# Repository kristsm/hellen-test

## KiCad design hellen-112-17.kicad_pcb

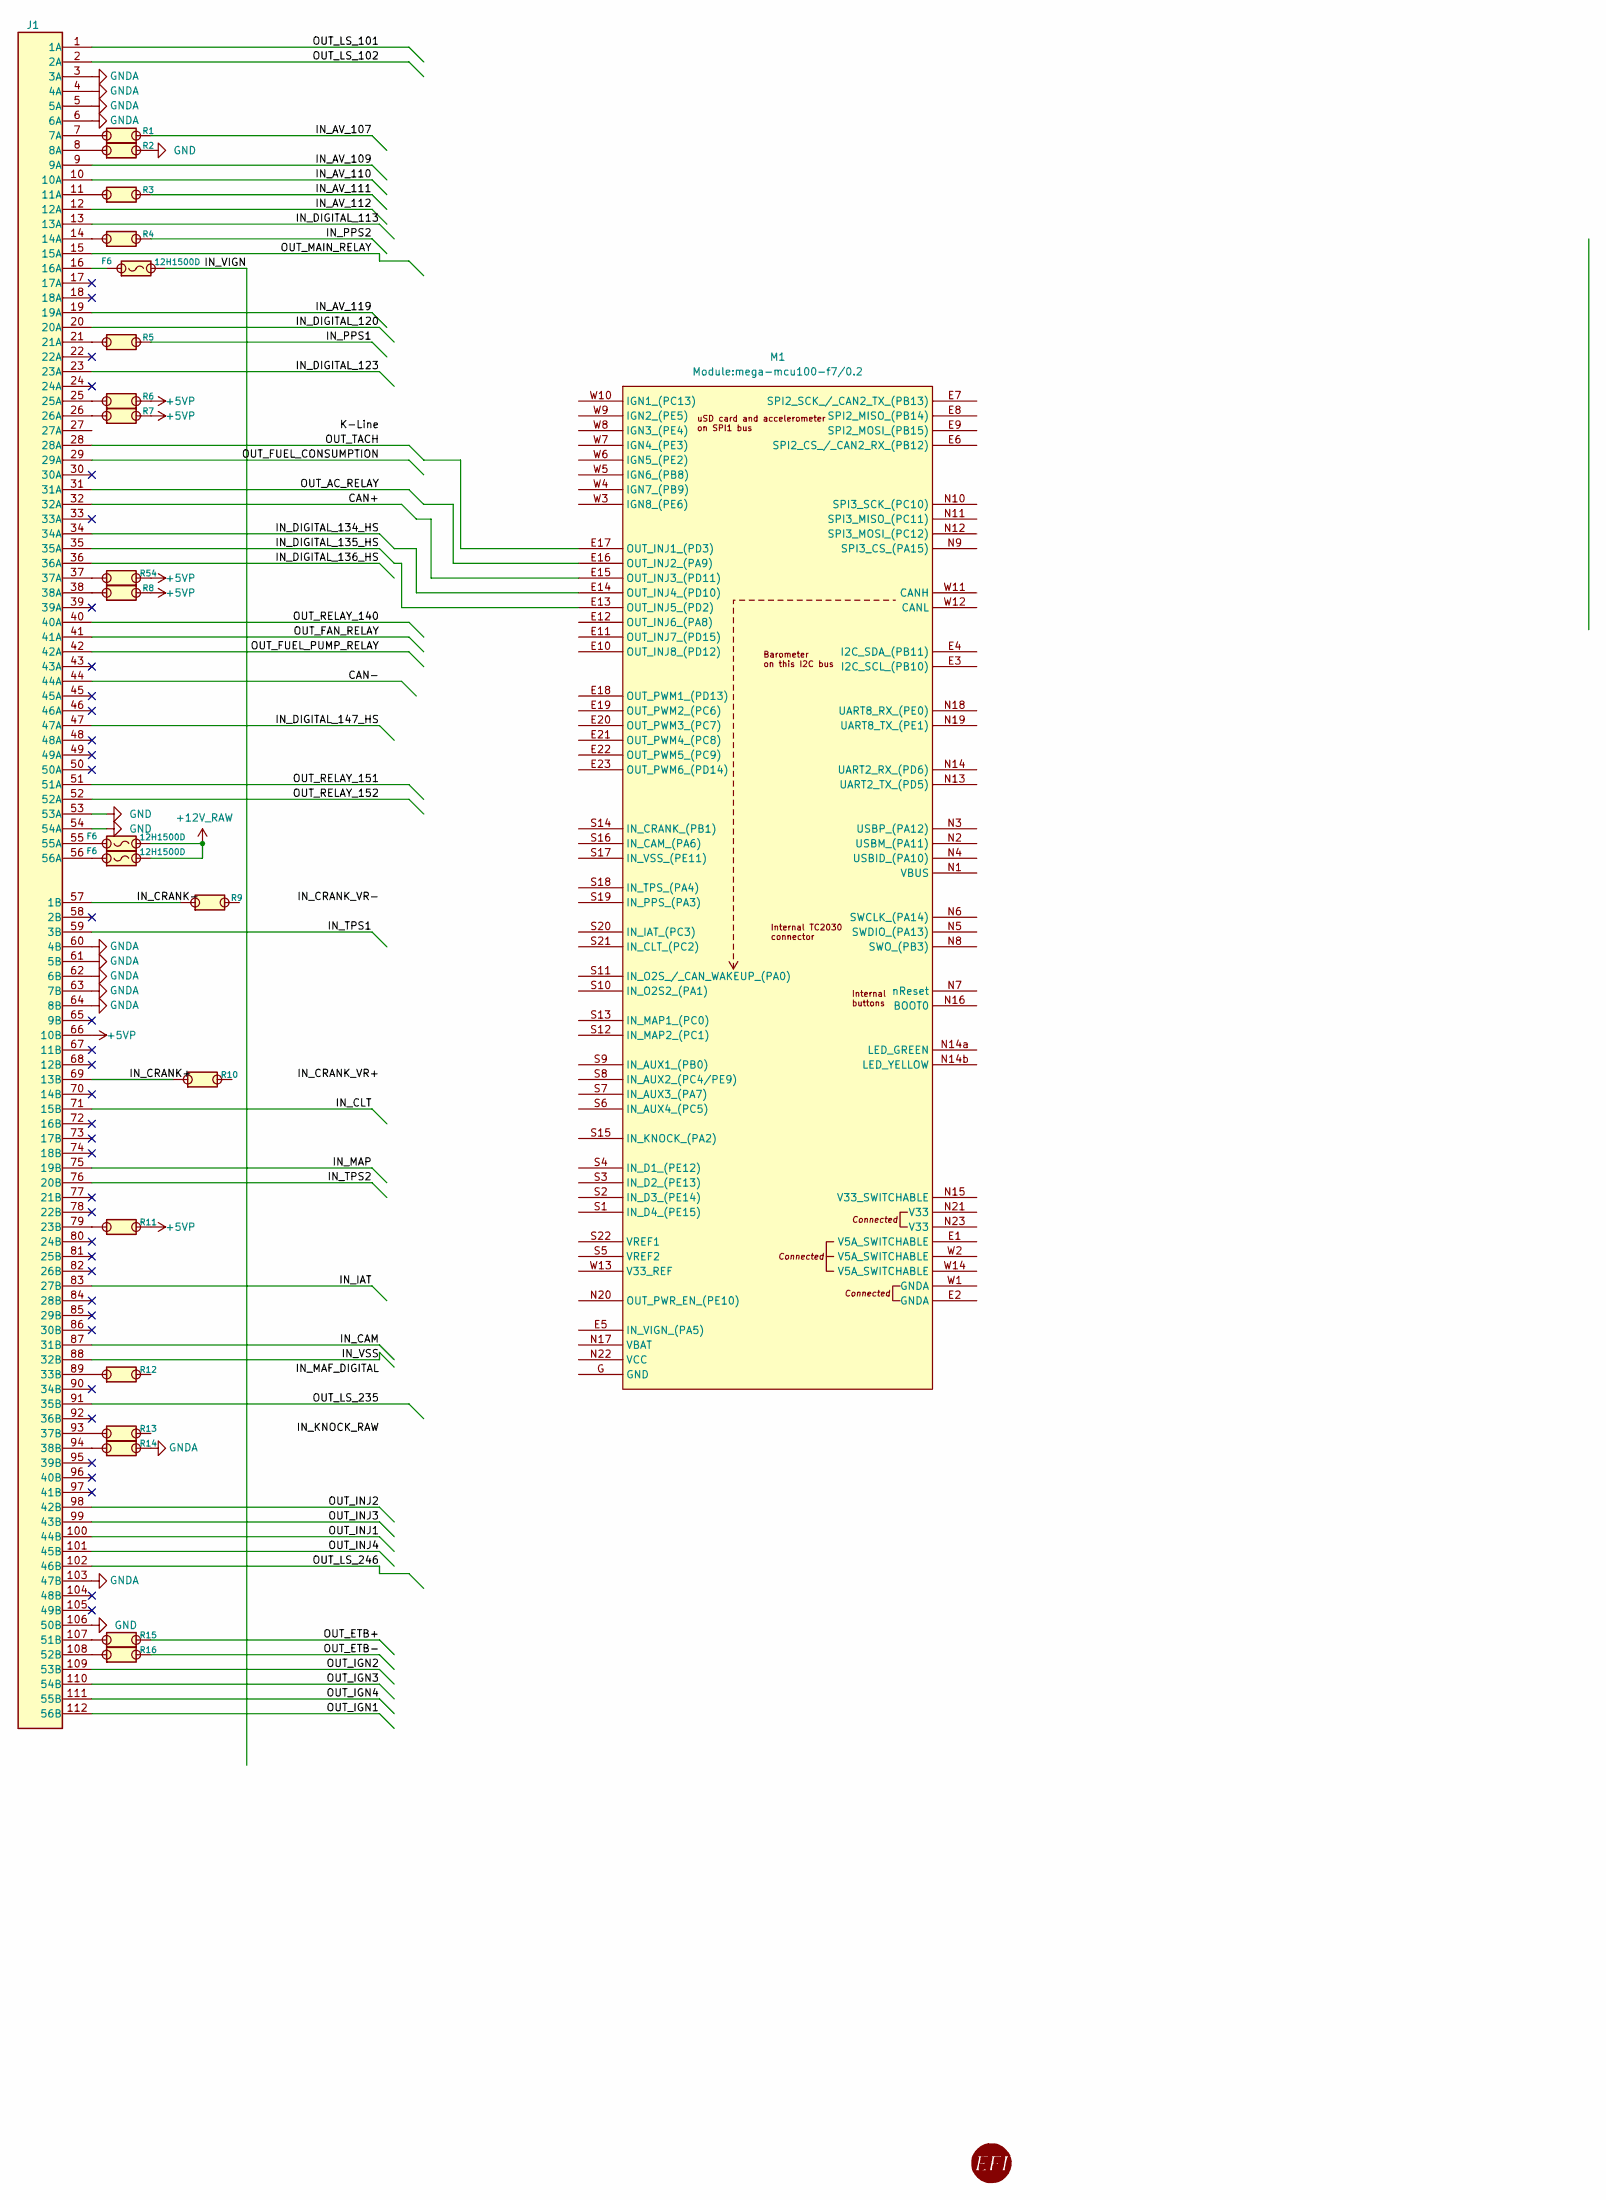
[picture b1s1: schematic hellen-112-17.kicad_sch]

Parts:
F6: 12H1500D; PAD-1206-PAD; LCSC C182446
G4: RUSEFI_LOGO; rusefi_logo
J1: rusefi_2x56_pin_conn; rusefi_2x56_pin_connector
M1: Module:mega-mcu100-f7/0.2; mega-mcu100-f7
R1, R2, R3, R4, R5, R6, R7, R8, R9, R10, R11, R12, R13, R14, R15, R16, R54: Jumper-Pad-Pad; PAD-0805-PAD; LCSC C17477

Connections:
+5VP: J1.66 (10B), R6.2, R7.2, R8.2, R11.2, R54.2
/CAN+: J1.32 (32A), M1.E15 (OUT_INJ3_(PD11))
/CAN-: J1.44 (44A)
/IN_AV_107: R1.2
/IN_AV_109: J1.9 (9A)
/IN_AV_110: J1.10 (10A)
/IN_AV_111: R3.2
/IN_AV_112: J1.12 (12A)
/IN_AV_119: J1.19 (19A)
/IN_CAM: J1.87 (31B)
/IN_CLT: J1.71 (15B)
/IN_CRANK+: J1.69 (13B), R10.1
/IN_CRANK-: J1.57 (1B), R9.1
/IN_DIGITAL_113: J1.13 (13A)
/IN_DIGITAL_120: J1.20 (20A)
/IN_DIGITAL_123: J1.23 (23A)
/IN_DIGITAL_134_HS: J1.34 (34A), M1.E14 (OUT_INJ4_(PD10))
/IN_DIGITAL_135_HS: J1.35 (35A), M1.E13 (OUT_INJ5_(PD2))
/IN_DIGITAL_136_HS: J1.36 (36A)
/IN_DIGITAL_147_HS: J1.47 (47A)
/IN_IAT: J1.83 (27B)
/IN_MAP: J1.75 (19B)
/IN_PPS1: R5.2
/IN_PPS2: R4.2
/IN_TPS1: J1.59 (3B)
/IN_TPS2: J1.76 (20B)
/IN_VSS: J1.88 (32B)
/OUT_AC_RELAY: J1.31 (31A), M1.E16 (OUT_INJ2_(PA9))
/OUT_ETB+: R15.2
/OUT_ETB-: R16.2
/OUT_FAN_RELAY: J1.41 (41A)
/OUT_FUEL_CONSUMPTION: J1.29 (29A)
/OUT_FUEL_PUMP_RELAY: J1.42 (42A)
/OUT_IGN1: J1.112 (56B)
/OUT_IGN2: J1.109 (53B)
/OUT_IGN3: J1.110 (54B)
/OUT_IGN4: J1.111 (55B)
/OUT_INJ1: J1.100 (44B)
/OUT_INJ2: J1.98 (42B)
/OUT_INJ3: J1.99 (43B)
/OUT_INJ4: J1.101 (45B)
/OUT_LS_101: J1.1 (1A)
/OUT_LS_102: J1.2 (2A)
/OUT_LS_235: J1.91 (35B)
/OUT_LS_246: J1.102 (46B)
/OUT_MAIN_RELAY: J1.15 (15A)
/OUT_RELAY_140: J1.40 (40A)
/OUT_RELAY_151: J1.51 (51A)
/OUT_RELAY_152: J1.52 (52A)
/OUT_TACH: J1.28 (28A), M1.E17 (OUT_INJ1_(PD3))
GND: J1.53 (53A), J1.54 (54A), J1.106 (50B), R2.2
GNDA: J1.3 (3A), J1.4 (4A), J1.5 (5A), J1.6 (6A), J1.60 (4B), J1.61 (5B), J1.62 (6B), J1.63 (7B), J1.64 (8B), J1.103 (47B), R14.2
unnamed: J1.7 (7A), R1.1
unnamed: J1.8 (8A), R2.1
unnamed: J1.11 (11A), R3.1
unnamed: J1.14 (14A), R4.1
unnamed 58: J1.16 (16A); also elsewhere on the board
unnamed: J1.21 (21A), R5.1
unnamed: J1.79 (23B), R11.1
unnamed: J1.25 (25A), R6.1
unnamed: J1.26 (26A), R7.1
unnamed: J1.89 (33B), R12.1
unnamed: J1.37 (37A), R54.1
unnamed: J1.93 (37B), R13.1
unnamed: J1.38 (38A), R8.1
unnamed: J1.94 (38B), R14.1
unnamed: J1.107 (51B), R15.1
unnamed: J1.108 (52B), R16.1
unnamed 70: J1.55 (55A); also elsewhere on the board
unnamed 71: J1.56 (56A); also elsewhere on the board

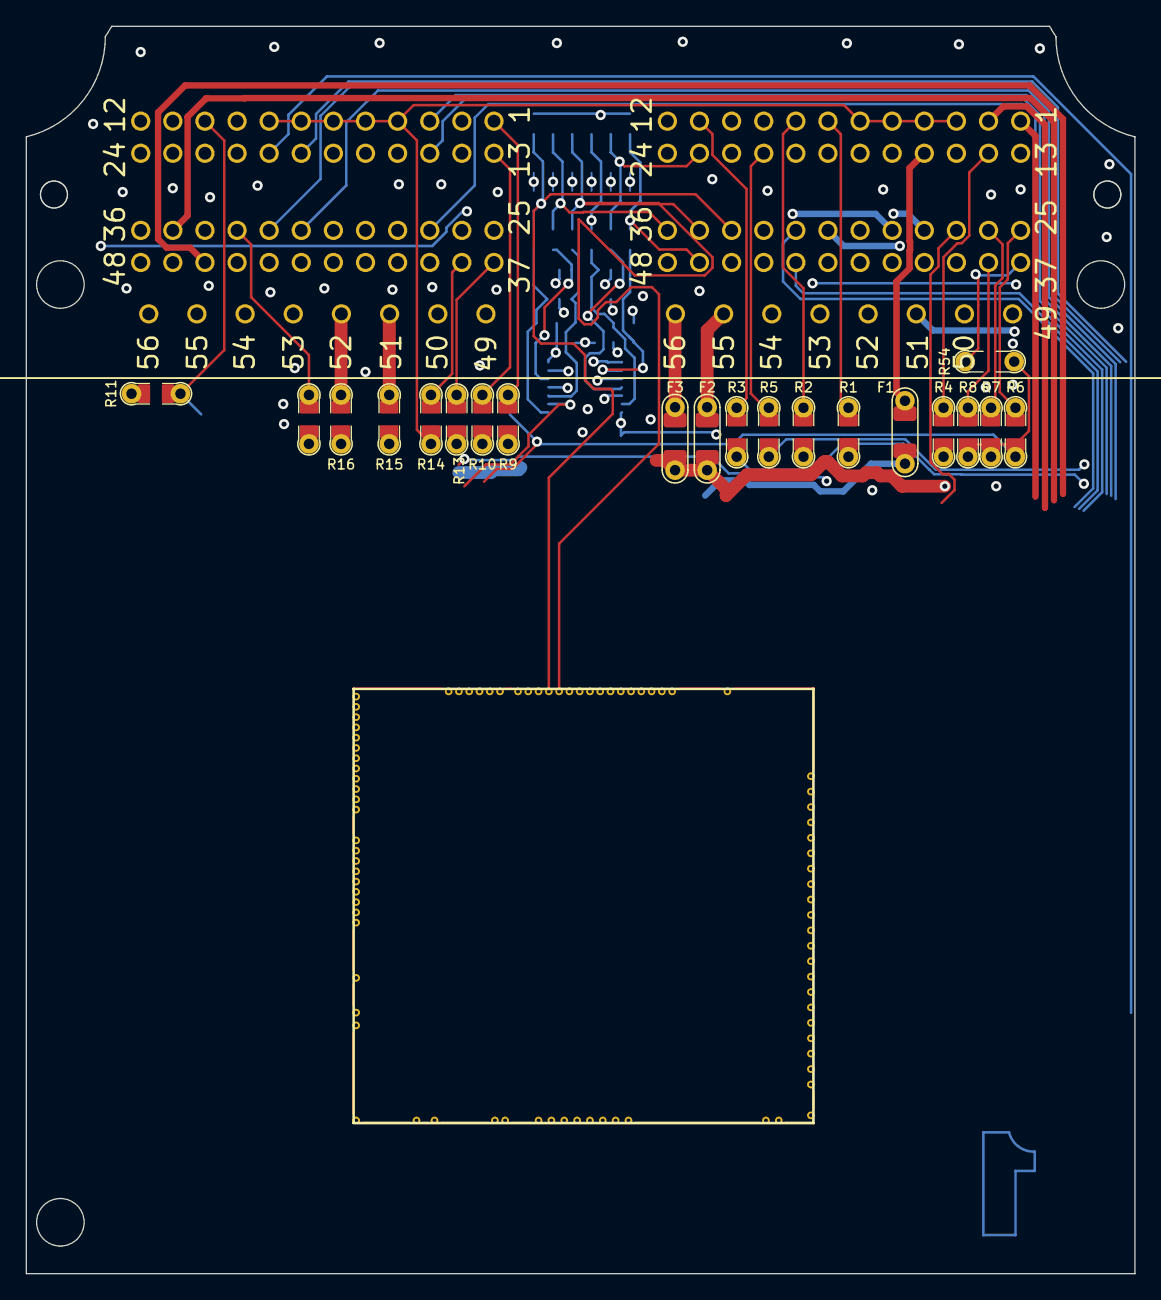
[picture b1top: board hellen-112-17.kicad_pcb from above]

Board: 4 copper layers, 86.3 x 97.1 mm, 22 parts (1 on the bottom side), 29 nets.

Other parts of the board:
F1, F2, F3: 12H1500D; PAD-1206-PAD

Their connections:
+12V_RAW: F2.2, F3.2
unnamed 58: F1.1; also elsewhere on the board
unnamed 70: F2.1; also elsewhere on the board
unnamed 71: F3.1; also elsewhere on the board

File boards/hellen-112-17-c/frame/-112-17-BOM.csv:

Comment,Designator,Footprint,LCSC Part #
"12H1500D","F1","PAD-1206-PAD","C182446"
"12H1500D","F2","PAD-1206-PAD","C182446"
"12H1500D","F3","PAD-1206-PAD","C182446"
"RUSEFI_LOGO","G4","rusefi_logo",""
"rusefi_2x56_pin_conn","J1","rusefi_2x56_pin_connector",""
"Jumper-Pad-Pad","R1","PAD-0805-PAD","C17477"
"Jumper-Pad-Pad","R2","PAD-0805-PAD","C17477"
"Jumper-Pad-Pad","R3","PAD-0805-PAD","C17477"
"Jumper-Pad-Pad","R4","PAD-0805-PAD","C17477"
"Jumper-Pad-Pad","R5","PAD-0805-PAD","C17477"
"Jumper-Pad-Pad","R6","PAD-0805-PAD","C17477"
"Jumper-Pad-Pad","R7","PAD-0805-PAD","C17477"
"Jumper-Pad-Pad","R8","PAD-0805-PAD","C17477"
"Jumper-Pad-Pad","R9","PAD-0805-PAD","C17477"
"Jumper-Pad-Pad","R10","PAD-0805-PAD","C17477"
"Jumper-Pad-Pad","R11","PAD-0805-PAD","C17477"
"Jumper-Pad-Pad","R12","PAD-0805-PAD","C17477"
"Jumper-Pad-Pad","R13","PAD-0805-PAD","C17477"
"Jumper-Pad-Pad","R14","PAD-0805-PAD","C17477"
"Jumper-Pad-Pad","R15","PAD-0805-PAD","C17477"
"Jumper-Pad-Pad","R16","PAD-0805-PAD","C17477"
"Jumper-Pad-Pad","R54","PAD-0805-PAD","C17477"

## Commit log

2024-11-30 3453
2024-11-30 [skip actions] Auto-generated board v2.1
2024-11-30 rev-c
2024-11-30 rev-d
